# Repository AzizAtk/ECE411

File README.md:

# ECE411 Audio Visualizer

Team 5

Team Members: Abdulaziz Alateeqi, Meshal Almutairi, Gene Hu, Flynn Flynn

## Project Overview
This project is a dynamic audio visualizer that reacts to the audio input signal in real-time, by illuminating an LED panel in patterns and colors corresponding to the audio’s signal. This device will be a must-have gadget for tech enthusiasts to upgrade their listening space. By utilizing digital signal processing and Fast Fourier Transforms, audio signals are displayed visually as beautiful LED arrays. Just plug the device into a standard DC USB block and turn on the power switch and the device is ready to operate.

## System Architecture

## CAD Design

## Software Design

### Audio
- The audio is sampled using I2S.

### FFT
- The FFT is implemented using the ArduinoFFT library.
- The FFT is used to convert the audio signal from the time domain to the frequency domain.
- The FFT is used to determine the amplitude of each frequency.

### LED Matrix
- The LED matrix is controlled using the FastLED and LEDMatrix libraries.
- The LED matrix is used to display the amplitude of each frequency as a bar graph.

## Prototype
<details>
  <summary>Click to expand prototype</summary>

</details>

## Design Specification

### Power Requirements
The project will require dedicated 5V 3A power that will need a dedicated AC wall adapter.
- A 2.1mm barrel jack will be mounted directly to the board.
- A standard USB to 2.1mm cable will attach to a Samsung USB block.
- The 5V will attach to the board via a trace (larger duty).

### Sensors
- The first input will be switchable between a 3.5mm TRS line level input.
  - This will run directly to Ain and Din on the ESP32.
  - The input TRS 3.5mm jack will be wired directly to a second TRS that routes audio to an external powered speaker.
- INMP441 microphone module.
- Inputs will be switchable with only one operating at a time.

### Actuators
- The output of the device will be an 8x32 LED matrix.
- The display will be a two-dimensional spectrogram.
  - The X-axis is the different frequencies.
  - The Y-axis is amplitude in volts.
- This will be done by individually addressing each light using each frequency as a logic parameter and the voltage reading to determine how many lights from that column illuminate.
- This will be on a purchased breakout board with power, ground, and address/clk line being connected to PCB via a 4-pin ribbon cable.

### Processing
- All processing will be done on an ESP32 microcontroller.
- Arduino IDE will be used as the programming environment.
- The controller will take in digital audio signals and process them into the frequency domain as a Fourier Transform.
- Different frequencies will be made into control loops for the program output.
- ESP32 will be mounted to the PCB via headers and sockets so the microcontroller can be removed for programming.

## Requirements

### Performance
- Must continuously visualize the input sound until switched off.
- Must be displaying accurate information (i.e., high LED bar if the frequency is overwhelming).
- Must be able to use a microphone to process the audio of surroundings.
- Should be able to take in sound through an audio jack.
  - Should have a speaker.

### User Experience
- Must be portable.
- Must be wall-powered through the adapter.
- Should be simple to use (plug and go).
- May use batteries.
  - May be rechargeable.

### Safety
- Must not overheat or be at risk of burning out LEDs.
- May be able to withstand being dropped lightly (No shattering?).

### Miscellaneous
- Should be able to switch the audio rails for input/output instead of having two separate lines.

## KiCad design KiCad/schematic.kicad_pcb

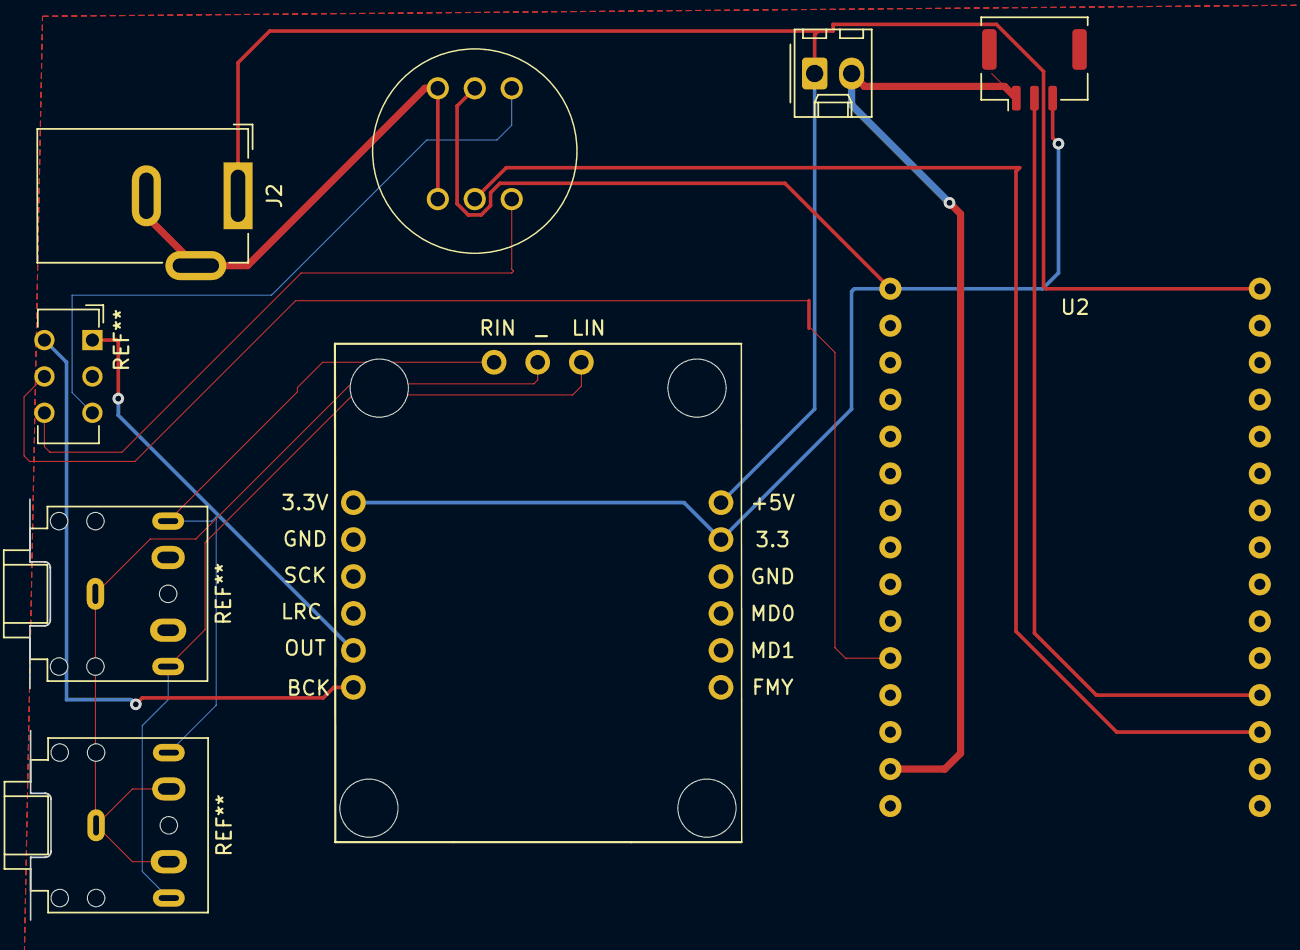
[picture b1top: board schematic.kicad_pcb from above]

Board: 2 copper layers, 4 parts (0 on the bottom side), 4 nets.

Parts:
J2: Barrel_Jack_Switch; BarrelJack_GCT_DCJ200-10-A_Horizontal
Mic1: INMP441
U1: CJMCU_FT232H
U2: ESP32-DOIT-DEVKIT

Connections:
+5V: J2.1, U1.+5V1, U2.L15, U2.R1
GND: J2.2, J2.3, Mic1.3 (GND), Mic1.L/R (SD), U1.GND, U2.L14, U2.R2, U2.R7
unnamed: Mic1.WS, U2.R13
VDD: Mic1.5 (VDD), U1.3.3, U1.3V3, U2.L1

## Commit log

2023-10-19 test commit
2023-10-19 add PDS, Oct 18 meeting log
2023-10-19 OCT 15 meeting log
2023-10-23 sunday 10/22 meeting log
2023-10-23 move logs to documents folder
2023-10-26 added KiCad folder
2023-10-26 updated files
2023-10-31 Add files via upload
    GanttProject file and a pdf of the latest version.
2023-11-01 add oct 30 meeting log, broadbaord prototype
2023-11-03 update CAD
2023-11-07 add func decomposition
2023-11-08 add initial source code
2023-11-09 nov 6 meeting log
2023-11-09 add BOM
2023-11-11 add mic and LED matrix tests
2023-11-13 add FFT analysis
2023-11-13 implement audio visualization
2023-11-30 update schematic pdf to final version
2023-11-30 add start screen, update visualizer look
2023-12-06 rename test plan
2023-12-07 updated test plan.pdf
2023-12-07 fix test plan cover page
2023-12-08 create LICENSE
